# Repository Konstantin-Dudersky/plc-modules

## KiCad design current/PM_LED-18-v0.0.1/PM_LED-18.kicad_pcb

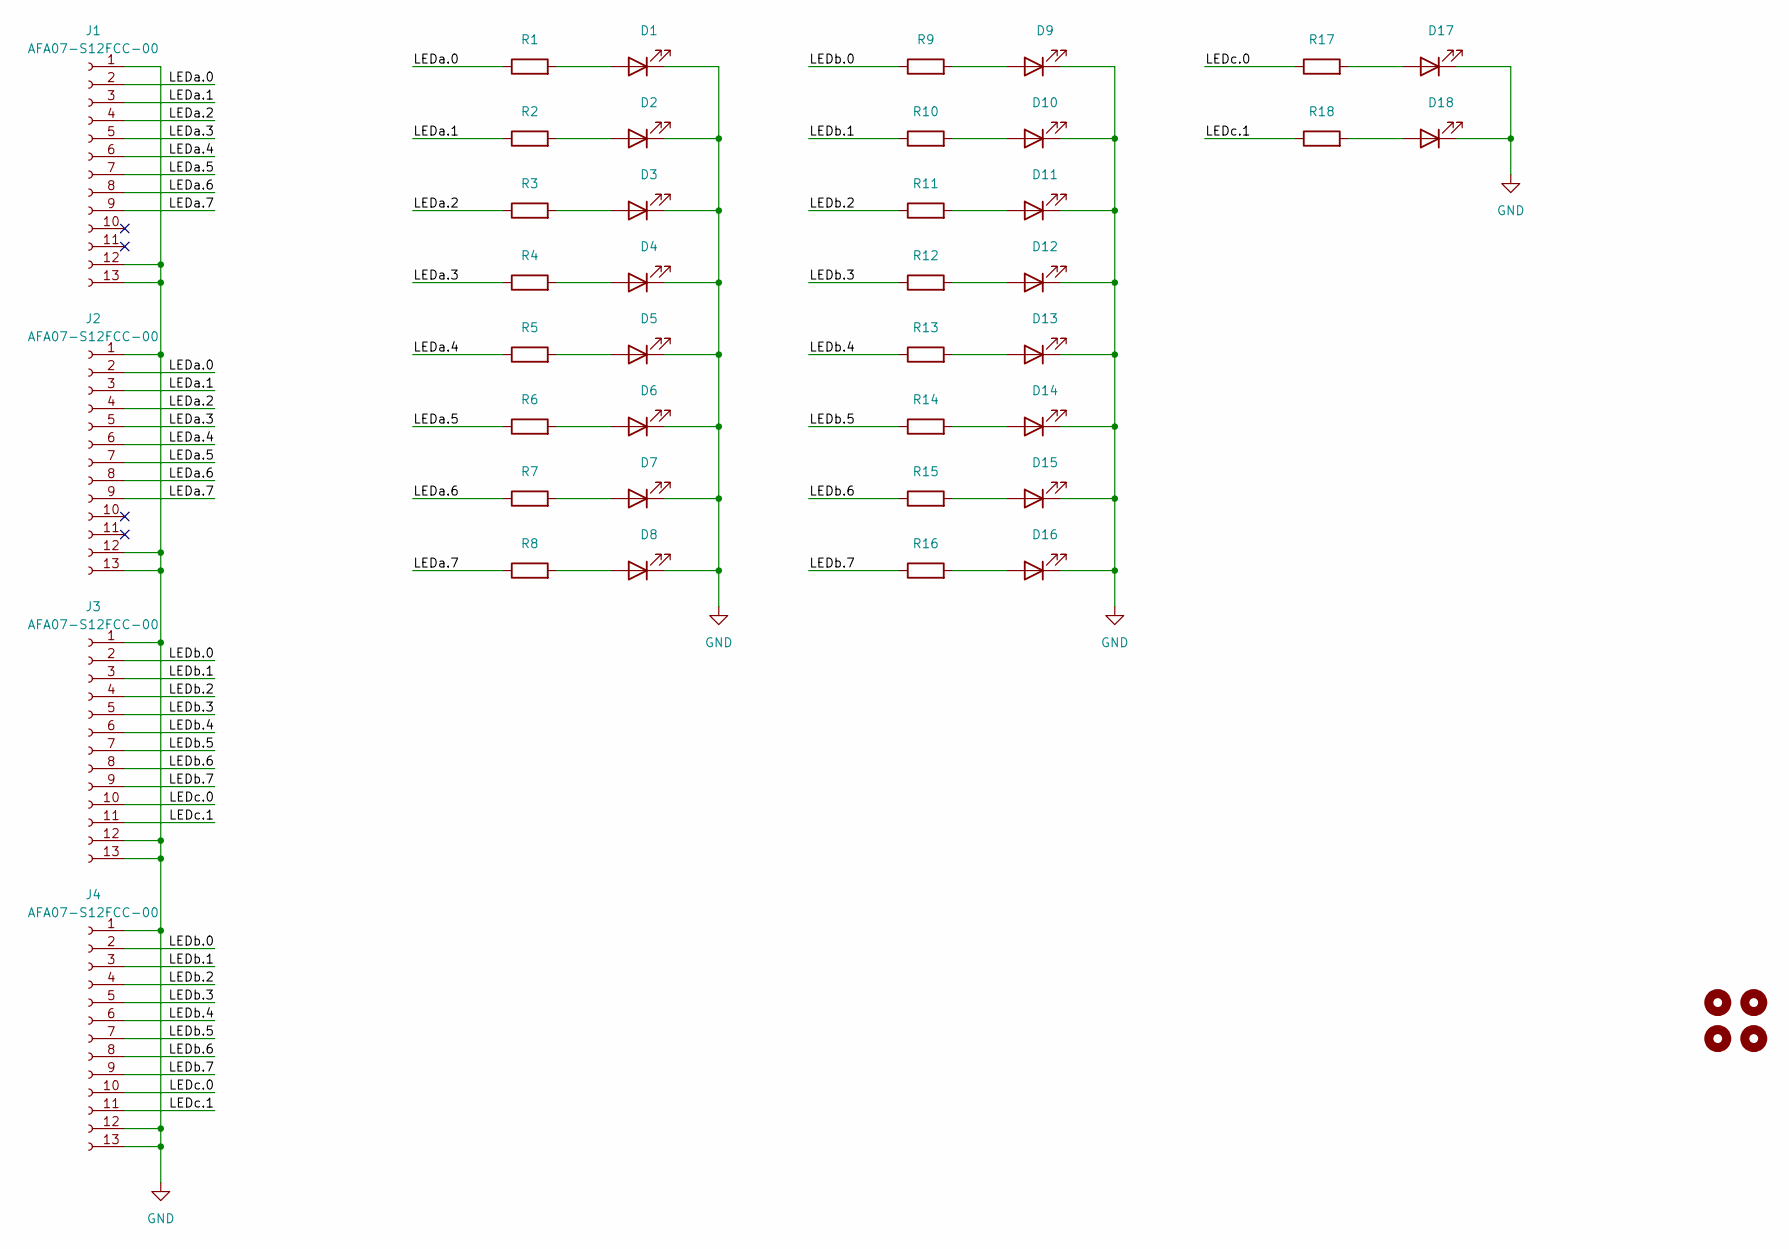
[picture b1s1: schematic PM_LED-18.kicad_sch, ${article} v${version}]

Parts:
D1, D2, D3, D4, D5, D6, D7, D8, D9, D10, D11, D12, D13, D14, D15, D16, D17, D18: XL-1606SYGC; XL-1606; part_ipn XL-1606SYGC
H1, H2, H3, H4: MountingHole_M2
J1, J2, J3, J4: AFA07-S12FCC-00; CONN10_AFA07-S12_JUS; part_ipn AFA07-S12FCC-00
R1, R2, R3, R4, R5, R6, R7, R8, R9, R10, R11, R12, R13, R14, R15, R16, R17, R18: R; R_0603_1608Metric

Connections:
/LEDa.0: J1.2, J2.2, R1.1
/LEDa.1: J1.3, J2.3, R2.1
/LEDa.2: J1.4, J2.4, R3.1
/LEDa.3: J1.5, J2.5, R4.1
/LEDa.4: J1.6, J2.6, R5.1
/LEDa.5: J1.7, J2.7, R6.1
/LEDa.6: J1.8, J2.8, R7.1
/LEDa.7: J1.9, J2.9, R8.1
/LEDb.0: J3.2, J4.2, R9.1
/LEDb.1: J3.3, J4.3, R10.1
/LEDb.2: J3.4, J4.4, R11.1
/LEDb.3: J3.5, J4.5, R12.1
/LEDb.4: J3.6, J4.6, R13.1
/LEDb.5: J3.7, J4.7, R14.1
/LEDb.6: J3.8, J4.8, R15.1
/LEDb.7: J3.9, J4.9, R16.1
/LEDc.0: J3.10, J4.10, R17.1
/LEDc.1: J3.11, J4.11, R18.1
GND: D1.1 (K), D2.1 (K), D3.1 (K), D4.1 (K), D5.1 (K), D6.1 (K), D7.1 (K), D8.1 (K), D9.1 (K), D10.1 (K), D11.1 (K), D12.1 (K), D13.1 (K), D14.1 (K), D15.1 (K), D16.1 (K), D17.1 (K), D18.1 (K), J1.1, J1.12 (Pin_11), J1.13 (Pin_11), J2.1, J2.12 (Pin_11), J2.13 (Pin_11), J3.1, J3.12 (Pin_11), J3.13 (Pin_11), J4.1, J4.12 (Pin_11), J4.13 (Pin_11)
unnamed: D1.2 (A), R1.2
unnamed: D2.2 (A), R2.2
unnamed: D3.2 (A), R3.2
unnamed: D4.2 (A), R4.2
unnamed: D5.2 (A), R5.2
unnamed: D6.2 (A), R6.2
unnamed: D7.2 (A), R7.2
unnamed: D8.2 (A), R8.2
unnamed: D9.2 (A), R9.2
unnamed: D10.2 (A), R10.2
unnamed: D11.2 (A), R11.2
unnamed: D12.2 (A), R12.2
unnamed: D13.2 (A), R13.2
unnamed: D14.2 (A), R14.2
unnamed: D15.2 (A), R15.2
unnamed: D16.2 (A), R16.2
unnamed: D17.2 (A), R17.2
unnamed: D18.2 (A), R18.2

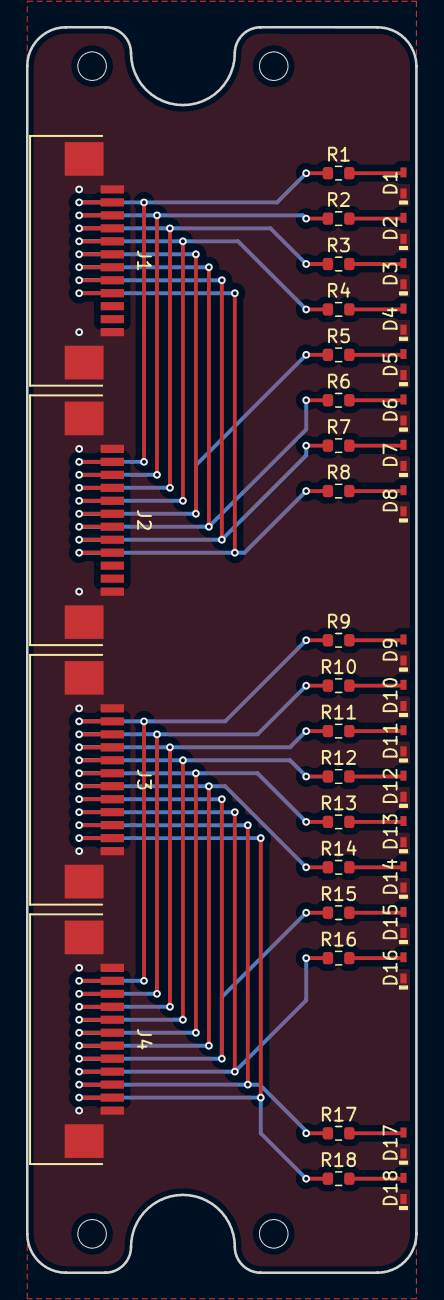
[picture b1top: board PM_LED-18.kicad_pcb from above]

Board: 2 copper layers, 30.0 x 96.0 mm, 45 parts (1 on the bottom side), 37 nets.

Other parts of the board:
Logo_kicad: KiCad-Logo2_5mm_SilkScreen

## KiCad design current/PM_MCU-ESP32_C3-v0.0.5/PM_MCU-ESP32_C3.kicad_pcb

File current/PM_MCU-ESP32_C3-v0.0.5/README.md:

v0.0.5:

- увеличил размеры платы на 0.1
- конденсаторы 10uF в типоразмере 0805
- тестовые пины для UART
- удалил 5В от USB
- поменял разъемы FCC с 10 на 12 пиновый
- ошибка - dip-переключатель замыкал пины накоротко

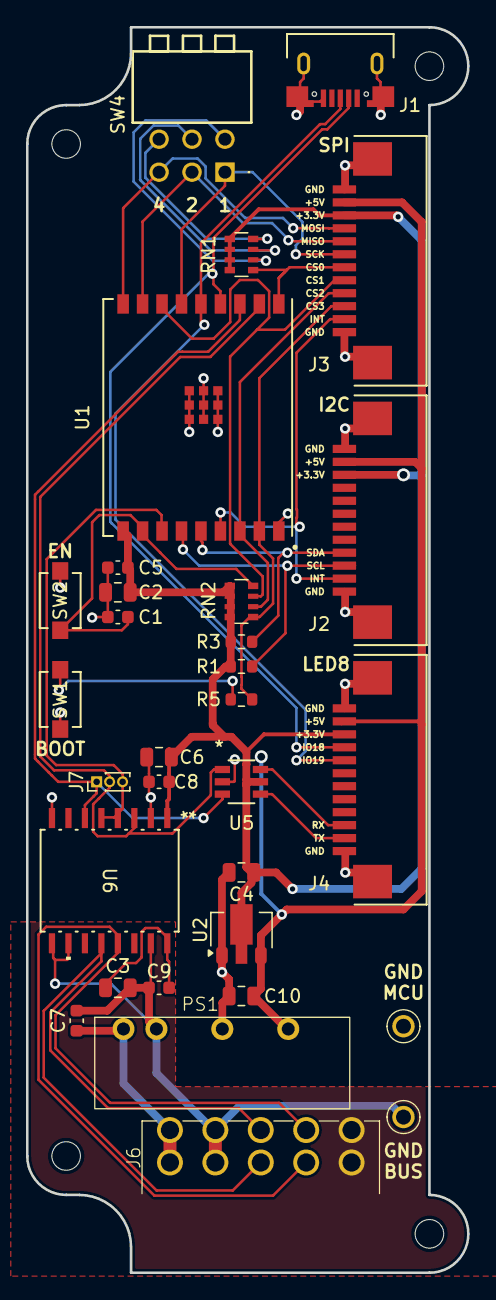
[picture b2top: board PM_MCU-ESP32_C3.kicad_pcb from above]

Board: 2 copper layers, 34.0 x 96.0 mm, 35 parts (0 on the bottom side), 31 nets.

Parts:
C1, C5, C7: 1uF; C_0603_1608Metric
C2, C3, C6, C10: 10uF; C_0805_2012Metric
C4: 22uF; C_0805_2012Metric
C8, C9: 100nF; C_0603_1608Metric
H1, H2, H3, H4: MountingHole_M2
J1: U254-051T-4BH83-S1S; CONN5_H83-S1S_XKB
J2, J3, J4: AFA07-S12FCC-00; CONN10_AFA07-S12_JUS
J6: 15EDGRHC-THR-3.5-10P
J7: PinHeader_01x03_P1.00_THT_straight; PinHeader_1x03_P1.00mm_Vertical
PS1: 24V/5V; B2405LS-1WR3
R1, R3: 3k3; R_0603_1608Metric
R5: 330R; R_0603_1608Metric
RN1, RN2: 10k; R_Array_Convex_4x0603
SW1, SW2: Button; SW_TS-1088_XNP-M
SW4: DIP 3 pos; DA03BLP
U1: ESP32-C3-WROOM-02U-N4; ESP32-C3-WROOM-02U_EXP
U2: CJA1117B-3.3; SOT-89-3
U3, U4: 5117
U5: SN74LVC2G14DBVR; DBV6-M
U6: CA-IS3098W; SOIC16-WBW_CLG

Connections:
+3.3V_BUS: C3.1, C9.1, U6.16 (VISO)
+3.3V_MCU: C2.1, C4.1, C5.1, C6.1, C8.1, J2.10, J3.10, J4.10, R1.1, R3.1, RN1.1 (R1.1), RN1.2 (R2.1), RN1.3 (R3.1), RN1.4 (R4.1), RN2.1 (R1.1), RN2.2 (R2.1), RN2.3 (R3.1), RN2.4 (R4.1), U1.1 (3V3), U2.2 (OUTPUT), U5.5 (VCC), U6.1 (VDD)
+5V_MCU: C10.1, J2.11, J3.11, J4.11, PS1.6 (+V), U2.3 (INPUT)
+24V_BUS: C7.1, J6.1, J6.6 (Pin_2), PS1.1 (Vin)
/A: J6.3, J6.8 (Pin_6), U6.12 (A)
/B: J6.4, J6.9 (Pin_8), U6.13 (B)
/CS0: J3.6, RN1.5 (R4.2), U1.10 (IO10)
/CS1: J3.5, RN2.7 (R2.2), U1.16 (IO2)
/CS2: J3.4, RN2.6 (R3.2), U1.7 (IO8)
/CS3: J3.3, R5.2, RN2.5 (R4.2), U1.8 (IO9)
/EN: C1.1, RN2.8 (R1.2), SW2.2, U1.2 (EN)
/INT: J2.2, J3.2, U1.6 (IO7)
/MISO: J3.8, SW4.2, U1.17 (IO1)
/MOSI: J3.9, SW4.3, U1.18 (IO0)
/SCK: J3.7, SW4.1, U1.15 (IO3)
/SCL: J2.3, R1.2, U1.4 (IO5)
/SDA: J2.4, R3.2, U1.5 (IO6)
/UART_RTS: J7.3, U1.3 (IO4), U6.4 (RE), U6.5 (DE)
/UART_RX: J7.2, U1.11 (RXD_(IO20)), U5.1 (1A), U6.3 (RO)
/UART_TX: J7.1, U1.12 (TXD_(IO21)), U5.3 (2A), U6.6 (DI)
/USB_D+: J1.3 (D+), J4.8, U1.14 (IO19_(USB_D+))
/USB_D-: J1.2 (D-), J4.9, U1.13 (IO18_(USB_D-))
GND_BUS: C3.2, C7.2, C9.2, J6.2 (Pin_3), J6.7 (Pin_4), PS1.2 (GND), U4.1, U6.9 (GNDB), U6.10 (SEL), U6.15 (GNDB)
GND_MCU: C1.2, C2.2, C4.2, C5.2, C6.2, C8.2, C10.2, J1.5 (GND), J2.1, J2.12 (Pin_11), J2.13 (Pin_11), J3.1, J3.12 (Pin_11), J3.13 (Pin_11), J4.1, J4.12 (Pin_11), J4.13 (Pin_11), PS1.4 (0V), SW1.1, SW2.1, U1.9 (GND), U1.EPAD, U2.1 (GND), U3.1, U5.2 (GND), U6.2 (GNDA), U6.8 (GNDA)
unnamed: J4.2, U5.4 (2Y)
unnamed: J4.3, U5.6 (1Y)
unnamed: R5.1, SW1.2
unnamed: RN1.8 (R1.2), SW4.4
unnamed: RN1.7 (R2.2), SW4.5
unnamed: RN1.6 (R3.2), SW4.6
PE: J6.5 (Pin_9), J6.10

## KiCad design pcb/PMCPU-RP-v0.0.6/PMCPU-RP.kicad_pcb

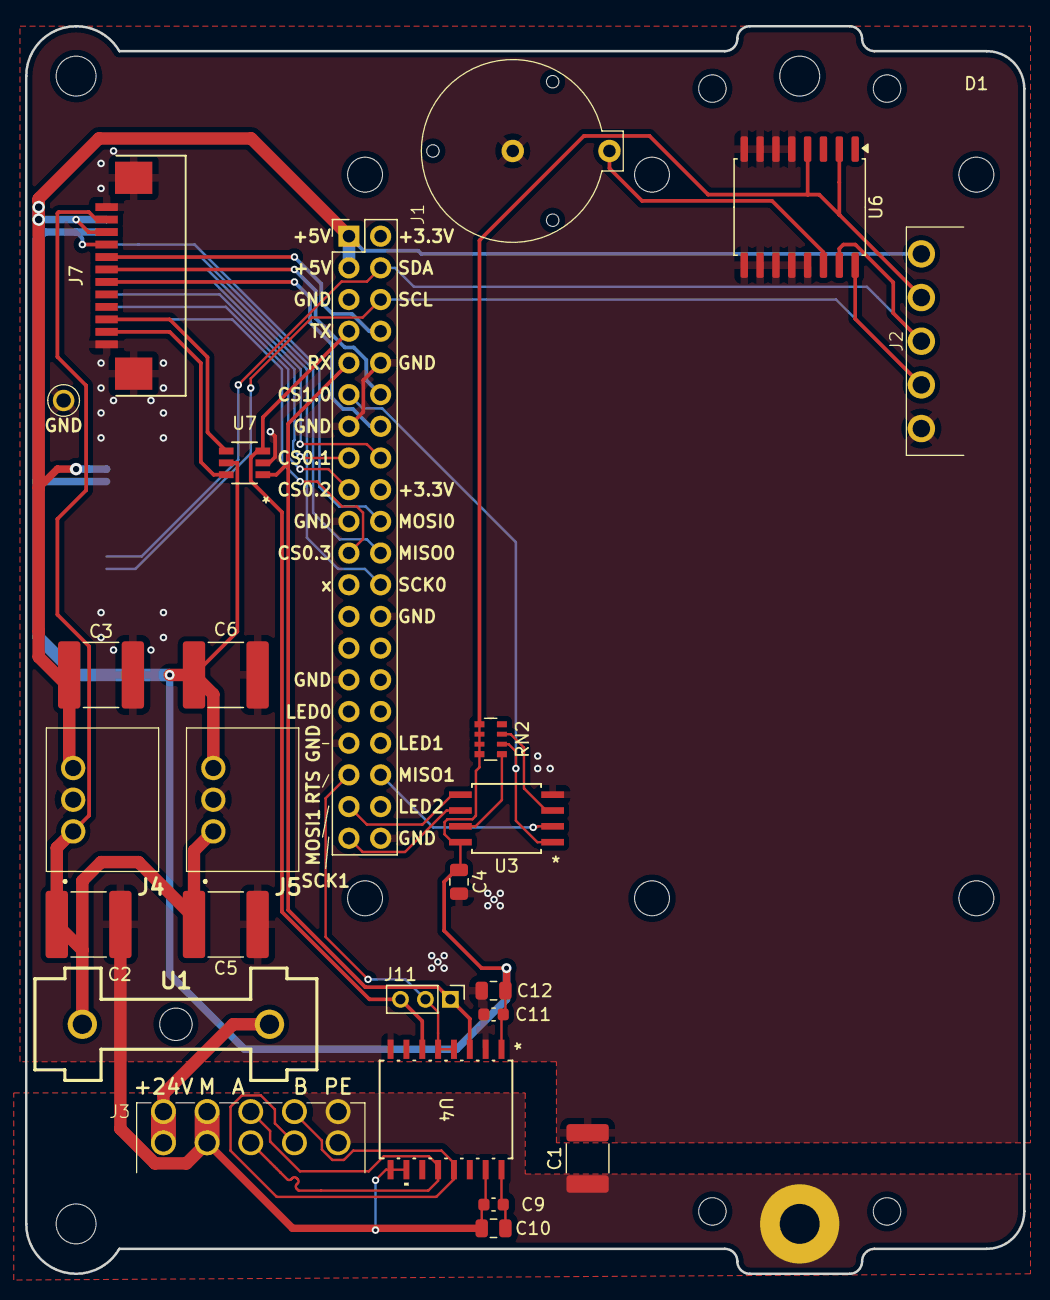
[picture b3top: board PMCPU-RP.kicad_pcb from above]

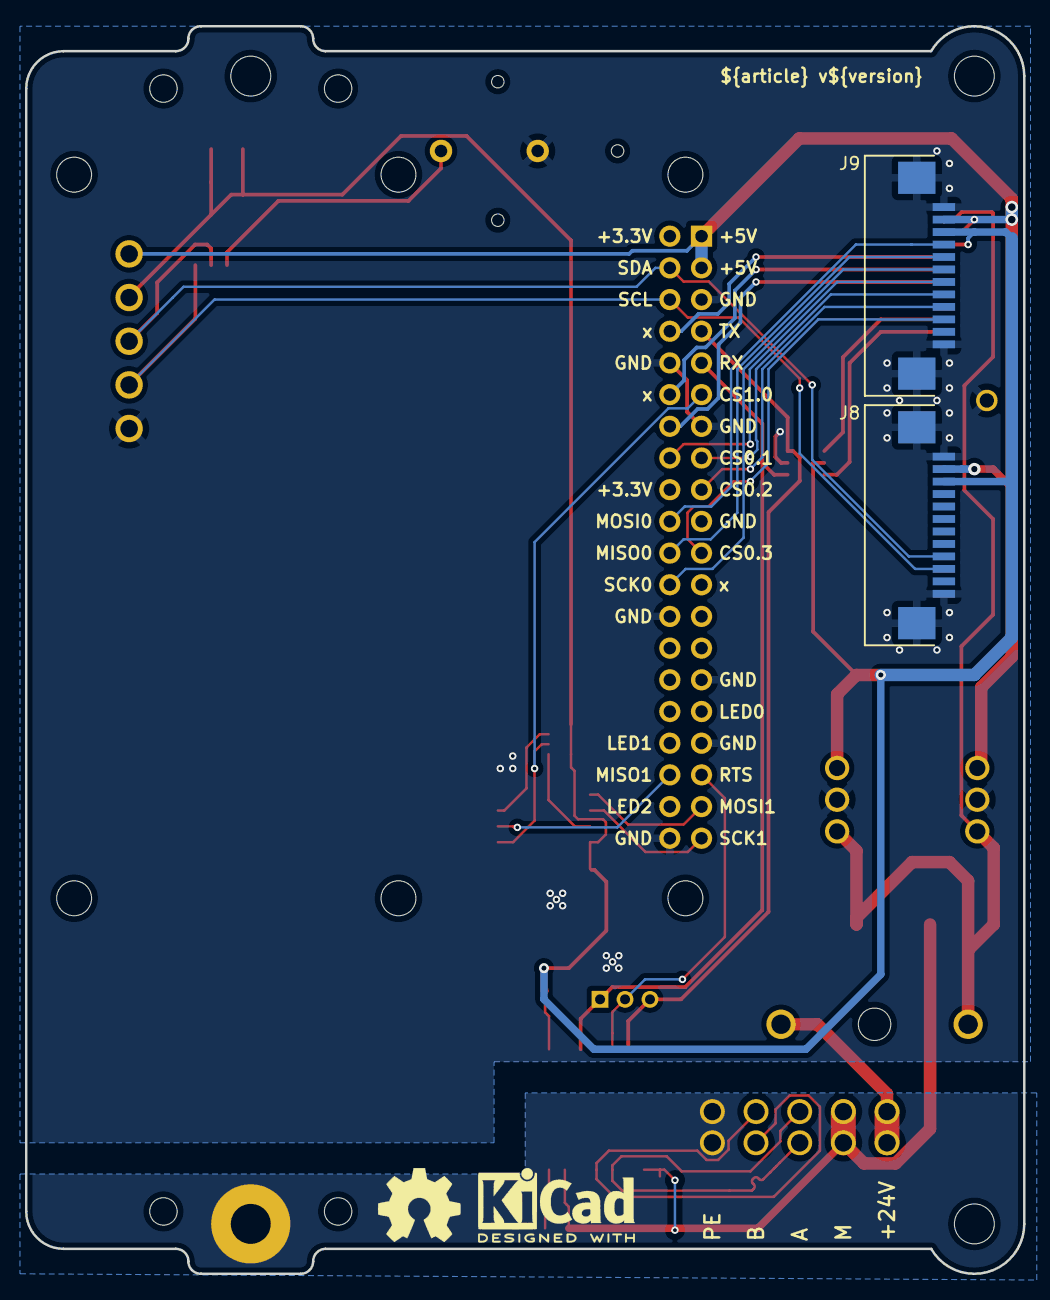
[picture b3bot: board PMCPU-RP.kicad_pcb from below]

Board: 2 copper layers, 80.0 x 100.0 mm, 34 parts (4 on the bottom side), 33 nets.

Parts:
C1: 4.7nF 2kV; C_1812_4532Metric
C2, C3, C5, C6: 22uF; C_2220_5750Metric
C4, C10, C12: 10uF; C_0805_2012Metric
C9, C11: 100nF; C_0603_1608Metric
D1: RaspberryPi
H1, H2, H3: MountingHole_M3
J1: BS-12-A1AJ002-F
J2: 15EDGRC-3.5-05P
J3: 15EDGRHC-THR-3.5-10P
J4: K7805-2000R3
J5: K7803-2000R3; K7805-2000R3
J7, J8, J9: AFA07-S10FCC-00; CONN10_AFA07-S12_JUS
J11: PinHeader_01x03_P2.00_THT_straight; PinHeader_1x03_P2.00mm_Vertical
PE1: PE
RN2: 10k; R_Array_Convex_4x0603
SP1: PM_LED-xx-v0.0.1
U1: 64900001039; 649-Series-Holder
U2: 5117
U3: W25Q32JVSSIQ; SOIC-8_5P28X5P28_WIN-M
U4: CA-IS3098W; SOIC16-WBW_CLG
U6: DS3231; SOIC-16W_7.5x10.3mm_P1.27mm
U7: SN74LVC2G14DBVR; DBV6-M
kicad_logo: KiCad-Logo2_5mm_SilkScreen
oshw_logo: OSHW-Symbol_6.7x6mm_SilkScreen

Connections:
+3.3V_BUS: C9.1, C10.1, U4.16 (VISO)
+3.3V_CPU: C4.1, C6.1, C11.1, C12.1, J2.4, J5.3 (+VO), J7.9, J8.3, J9.3, RN2.5 (R4.2), RN2.6 (R3.2), RN2.7 (R2.2), RN2.8 (R1.2), U3.8 (VCC), U4.1 (VDD), U6.2 (VCC), U6.4 (~RST), U7.5 (VCC)
+5V_CPU: C3.1, D1.2 (5V), D1.4 (5V), J2.5, J4.3 (+VO), J7.10, J8.2, J9.2
+24V_BUS: J3.1, J3.6 (Pin_2), U1.1
+24V_fuse: C2.1, C5.1, J4.1 (VIN), J5.1 (VIN), J7.11, U1.2
/A: J3.3, J3.8 (Pin_6), U4.12 (A)
/B: J3.4, J3.9 (Pin_8), U4.13 (B)
/LED_0: D1.7 (GPIO4/GPCLK0), J7.8
/LED_1: D1.11 (GPIO17), J7.7
/LED_2: D1.13 (GPIO27), J7.6
/SCL: D1.5 (GPIO3/I2C_SCL), J2.2, J8.10, U6.16 (SCL)
/SDA: D1.3 (GPIO2/I2C_SDA), J2.3, J8.9, U6.15 (SDA)
/SPI0_CS0: D1.15 (GPIO22), J9.7
/SPI0_CS1: D1.16 (GPIO23), J9.8
/SPI0_CS2: D1.18 (GPIO24), J9.9
/SPI0_CS3: D1.22 (GPIO25), J9.10
/SPI0_MISO: D1.21 (GPIO9/SPI_MISO), J9.5
/SPI0_MOSI: D1.19 (GPIO10/SPI_MOSI), J9.4
/SPI0_SCK: D1.23 (GPIO11/SPI_SCLK), J9.6
/SPI1_CS0: D1.12 (GPIO18/PCM_CLK), RN2.2 (R2.1), U3.1 (/CS)
/SPI1_MISO: D1.35 (GPIO19/PCM_FS), U3.2 (DO(IO1))
/SPI1_MOSI: D1.38 (GPIO20/PCM_DIN), U3.5 (DI(IO0))
/SPI1_SCK: D1.40 (GPIO20/PCM_DOUT), U3.6 (CLK)
/UART_RTS: D1.36 (GPIO16), J11.2, U4.4 (RE), U4.5 (DE)
/UART_RX: D1.10 (GPIO15/UART_RX), J11.1, U4.3 (RO), U7.1 (1A)
/UART_RX_LED: J7.2, U7.6 (1Y)
/UART_TX: D1.8 (GPIO14/UART_TX), J11.3, U4.6 (DI), U7.3 (2A)
/UART_TX_LED: J7.3, U7.4 (2Y)
/Vbat: J1.1, U6.14 (VBAT)
GND_BUS: C1.2, C2.2, C3.2, C4.2, C5.2, C6.2, C9.2, C10.2, C11.2, C12.2, D1.6 (GND), D1.9 (GND), D1.14 (GND), D1.20 (GND), D1.25 (GND), D1.30 (GND), D1.34 (GND), D1.39 (GND), J1.2, J2.1, J3.2 (Pin_3), J3.7 (Pin_4), J4.2 (GND), J5.2 (GND), J7.1, J7.12 (Pin_11), J7.13 (Pin_11), J8.1, J8.12 (Pin_11), J8.13 (Pin_11), J9.1, J9.12 (Pin_11), J9.13 (Pin_11), U2.1, U3.4 (GND), U4.2 (GNDA), U4.8 (GNDA), U4.9 (GNDB), U4.10 (SEL), U4.15 (GNDB), U6.5 (GND), U6.6 (GND), U6.7 (GND), U6.8 (GND), U6.9 (GND), U6.10 (GND), U6.11 (GND), U6.12 (GND), U6.13 (GND), U7.2 (GND)
unnamed: RN2.1 (R1.1), U3.7 (/HOLD_(IO3))
unnamed: RN2.3 (R3.1), U3.3 (/WP(IO2))
PE: C1.1, J3.5 (Pin_9), J3.10, PE1.1
